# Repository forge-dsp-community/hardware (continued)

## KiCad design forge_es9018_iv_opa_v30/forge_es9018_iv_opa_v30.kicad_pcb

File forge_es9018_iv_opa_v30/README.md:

# Forge ES9018 I/V-Ausgangsplatine V3.0 (96ELN) – KiCad-Rekonstruktion

| Seite F | Seite B |
|---|---|
|  |  |

3D-Renderings aus KiCad (`kicad-cli pcb render --rotate '-35,0,±30' --zoom 0.9 --background opaque`). C5…C8 sind wie auf den realen Platinen 0-Ω-Brücken auf den Elko-Plätzen.

## Herkunft

Quelle: `forge/pcbs/output/eln/V30` (bitbucket.org/forge-dsp/pcbs, Mark Duprau, Lizenz CC BY-NC-SA 4.0).
Diese Rekonstruktion steht unter derselben Lizenz.

Diese I/V-Ausgangsplatine wird in einen der 4 Steckplätze J1–J4 der AD/DA-Trägerplatine gesteckt
(siehe `../forge_es9018_pcm4202_ad_v40`). Dort sitzt der ES9018 bzw. ES90x8.
Die Platine wandelt zwei differentielle DAC-Stromausgänge in zwei symmetrische Spannungsausgänge um.

## Schaltung (je Kanal, Kanal 2 / Kanal 1)

| Stufe | Bauteile | Wert |
|---|---|---|
| I/V-Wandler (+ Eingang an I.x-VREF) | R1/R2 bzw. R5/R6 (Rückkopplung) | 2720R 0.1% 10ppm |
| | R102…R105 + C116…C119 (Serienglied parallel zur Rückkopplung) | 100R 0.1% + 100pF C0G |
| Elkoplatz, mit 0R überbrückt (nur V30) | C5…C8 zwischen I/V-Ausgang und 470R | Auf realen Platinen mit 0-Ω-SMD (1206) auf den THT-Pads bestückt statt mit Elko |
| Filter | R106…R109 / C1…C4 | 470R 0.1% / 100nF C0G |
| Differenzverstärker | R114…R117 (Eingang), R110…R113 (Rückkopplung bzw. nach AGND) | 20R 1% / 360R 0.1% |
| | C122…C125 + R3, R4, R7, R8 | 3.9nF C0G + 100R 0.1% |
| VREF-Abblockung | C9, C10 | Wert im Original nicht angegeben |
| Versorgung | C110…C115 | 100nF 16V |

Steckzunge X1 (13 Kontakte, links → rechts): O.2+, O.2−, O.1+, O.1−, −12V, GND, +12V, I.1−, I.1−VREF, I.1+, I.2−, I.2−VREF, I.2+.
O.x− und GND liegen auf AGND.

## Vorgehen

* Quelle sind nur die Eagle-Renderings im Repo (300 dpi): Kupferlagen, Vias, Durchsteckpads (`PADS`), Bestückungsdruck, das Gesamtbild und das Schaltplanbild. Gerber-Bilder gibt es für diese Platine nicht.
* SMD-Pads und Bauteilmitten stammen aus dem Gesamtbild, SOIC-Gehäuse aus den Pinreihen.
  Die Opamp-Ausrichtung ergibt sich aus den ±12-V-Kontakten der Steckzunge.
* Netze ergeben sich aus den Kupfer-Inseln je Lage, verbunden über Vias.
* **Referenzen und Werte** wurden über die Schaltungstopologie den Originalbezeichnungen zugeordnet.
  Beispiel: Ein Widerstand zwischen dem − Eingang und dem Ausgang einer I/V-Sektion ist R1/R2/R5/R6.
  Alle 48 passiven Bauteile des Original-Schaltplans wurden gefunden und zugeordnet.
* Kupfer liegt als **Leiterbahnen** vor (463 Leiterbahn-Segmente, 66 Flächen-Zonen). Breite Flächen (im Original Eagle-Polygone, auch Via-Felder) sind **Zonen mit Netz**, die KiCad selbst füllt (Clearance 0,08 mm, Thermals an THT-Pads). Schaltplan und Platine sind verknüpft.
  Erzeugt mit `rekonstruktion/tracks.py` aus `polys.json`:
  Jede Kupferinsel wird mit 25 px/mm gerastert. Flächen werden über den Distanz-Transform erkannt (morphologisches Öffnen), der Rest wird skelettiert (Zhang-Suen), in Pfade zwischen End- und Knotenpunkten zerlegt, mit Douglas-Peucker vereinfacht, kurze Sporne fallen weg.
  Spurbreite = 2 × Distanz-Transform (Median), abgerundet auf Eagle-Breiten (0,1524 … 1,016 mm) und zusätzlich so begrenzt, dass Clearance zu fremdem Kupfer und Randabstand passen. Über das eigene Kupfer hinaus darf eine Spur höchstens bis zur Hälfte der Lücke zum Nachbarn ragen.
  Endpunkte an Pads/Vias desselben Netzes rasten auf die Pad-/Via-Mitte ein, an Flächen werden sie 0,3 mm hinein verlängert.
  Fläche wird, was einschließlich Pads und Vias ≥ 1,2 mm breit ist, dazu angrenzendes Kupfer ab 0,9 mm Breite. Danach rastert das Skript die erzeugten Spuren und vergleicht sie mit dem Originalkupfer (Formprüfung): Bleibt ein dicker Bereich (≥ 0,3 mm dick, ≥ 0,15 mm²) unbedeckt, wird er mit 0,5 mm Umgebung zur Fläche und die Insel neu berechnet. So werden Via-Felder Flächen statt Haufen kurzer breiter Spuren.
  Die Bild-Pads sind oft größer als die Footprint-Pads, manche Vias liegen direkt am Pad. Was nach dem Skelett innerhalb einer Insel noch getrennt ist, verbindet das Skript deshalb über einen kürzesten Weg durch das Originalkupfer.
  Zum Schluss prüft das Skript mit dem KiCad-DRC und macht Spuren mit Clearance- oder Randfehlern schrittweise schmaler. Spuren, die schon 0,1 mm breit sind, schiebt es um das fehlende Stück vom Hindernis weg.
  Die frühere Zonen-Fassung liegt als `rekonstruktion/forge_es9018_iv_opa_v30_zonen.kicad_pcb` bei. Neu erzeugen mit `/usr/bin/python3 rekonstruktion/tracks.py .`; das Skript liest immer die Zonen-Fassung.

## Prüfung

* DRC (`kicad-cli pcb drc --refill-zones --schematic-parity`): keine offenen Verbindungen, keine Kurzschlüsse, keine Clearance-Fehler, Schaltplan-Abgleich ohne Abweichungen, also wie mit den Zonen.
  Warnungen: 12 × Druck über Kupfer bzw. am Rand (Original-Bestückungsdruck), 4 × „Leiterbahn mit offenem Ende“. Das sind Sackgassen im Originalkupfer (Masse-Randstreifen, AGND-Finger).
* ERC: 0 Verstöße

## Schaltplan

`rekonstruktion/sch_layout.py` ordnet den aus `sch.py` erzeugten Schaltplan neu an (A3):

* OpAmps sind IC-Kästen mit allen 8 bzw. 14 Pins in Gehäusefolge (links 1…4 bzw. 1…7 von oben, rechts gegenläufig). Die Symbole `OPA_DUAL`/`OPA_QUAD` in `forge_iv_opa.kicad_sym` wurden dafür ersetzt.
* Je OpAmp-Sektion liegt die Rückkopplung (R, RC-Glied) außen neben ihren drei Pins, auf der Seite des Ausgangs. Vom Ausgang laufen Koppel-C, Filterwiderstand und Filterknoten mit Querkondensator in einer Reihe nach außen. Die Eingangsbeschaltung liegt auf der anderen Seite.
* Die Abblockkondensatoren hängen per Draht am V+/V−-Pin des OpAmps, an dem sie auf der Platine sitzen.
* Globale Labels gibt es nur zwischen den Gruppen (OpAmp-Blöcke und Steckzunge X1). Versorgung erscheint als Power-Symbole.
* Verdrahtete Netze tragen ihren Namen als lokales Label (`/NAME`). Die Netznamen der Platine sind daran angeglichen (`sch_layout.py <projekt> --pcb`, ändert `.kicad_pcb` und die Zonen-Sicherung). Der DRC mit Schaltplan-Abgleich ist ohne Abweichung.
* Die Netzliste ist geprüft identisch mit der vorherigen Label-Fassung (`rekonstruktion/<name>_labels.kicad_sch`). Die ERC ist ohne Fehler.

## Hinweise

* 2 Lagen. **U2 = LME49740** (Quad, SOIC-14, alle 4 I/V-Stufen, V+ an Pin 4, V− an Pin 11).
  **U1 = LME49720** (Dual, SOIC-8, Differenzverstärker beider Kanäle, V+ an Pin 8, V− an Pin 4).
  Die Typen stammen vom Nutzer. Die Pinbelegung ist gegen beide Datenblätter geprüft (LME49720 von TI, LME49740 von National, Connection Diagram):
  V+/V− und alle + Eingänge (VREF) bzw. − Eingänge (I.x±) liegen auf den Pins, die die Datenblätter angeben.
  Das Datenblatt-Feld ist in Symbol und Footprint eingetragen.
* C5…C8 sind im Bestückungsdruck Elko-Plätze (Plus zum 470R, quadratisches Pad Minus). Auf realen Platinen sitzt dort aber ein 0-Ω-SMD-Widerstand, die I/V-Stufen sind also DC-gekoppelt; den Gleichanteil hebt der Differenzverstärker auf. Schaltplan (Symbol R, Wert „0R (Brücke)“), Footprint `R_0R_auf_Elkoplatz_TH_P2.55` (Elko-Pads, 3D-Modell 1206) und die Generatoren (`outnaming.py`, `pcb.py`, `sch.py`, `models3d.py`) bilden das ab. Die Netze IVx±/IVx±_AC bleiben getrennt benannt.
* Die Symbole sind generische Dual-/Quad-OpAmp-Symbole (IC-Kasten mit allen Pins in Gehäusefolge) mit den Pinfunktionen nach Datenblatt; der Wert trägt den Typ.
* Einige SMD-Pads liegen teilweise unter dem Bestückungsdruck. Ihre Größe ist aus dem Bild geschätzt (±0,05 mm); die Pad-Mitten passen zum Kupfer.
* Skripte und Modell liegen in `rekonstruktion/`. Neu erzeugen mit `build_out.sh V30` (ergibt die Zonen-Fassung), danach `rekonstruktion/forge_es9018_iv_opa_v30_zonen.kicad_pcb` löschen und `/usr/bin/python3 rekonstruktion/tracks.py .` ausführen; die Pfade in `build_out.sh` zeigen auf das temporäre Arbeitsverzeichnis der Sitzung.

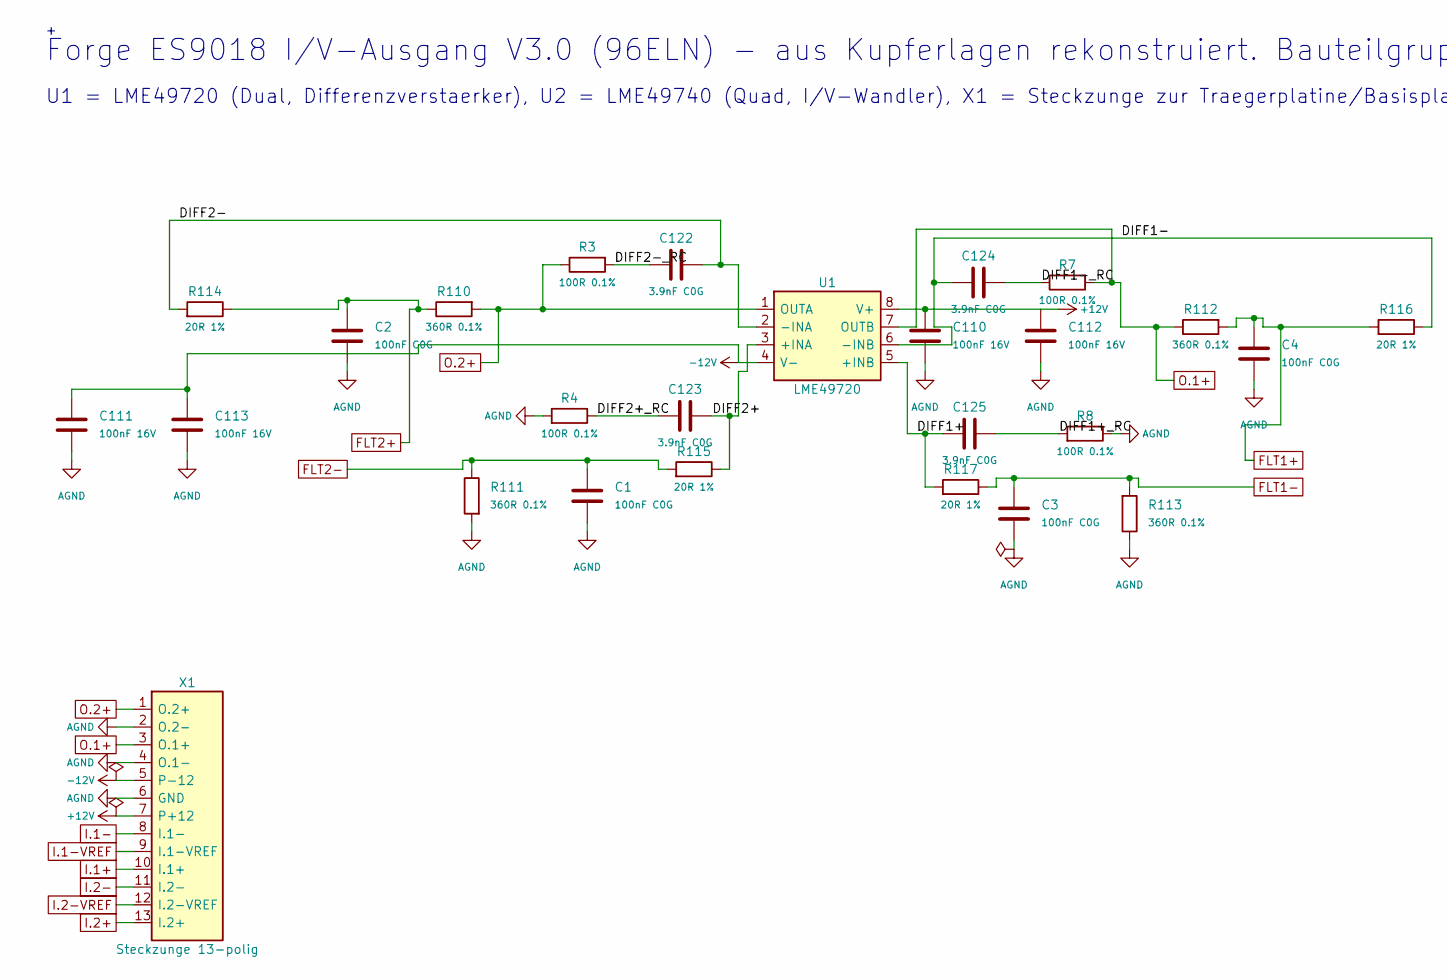
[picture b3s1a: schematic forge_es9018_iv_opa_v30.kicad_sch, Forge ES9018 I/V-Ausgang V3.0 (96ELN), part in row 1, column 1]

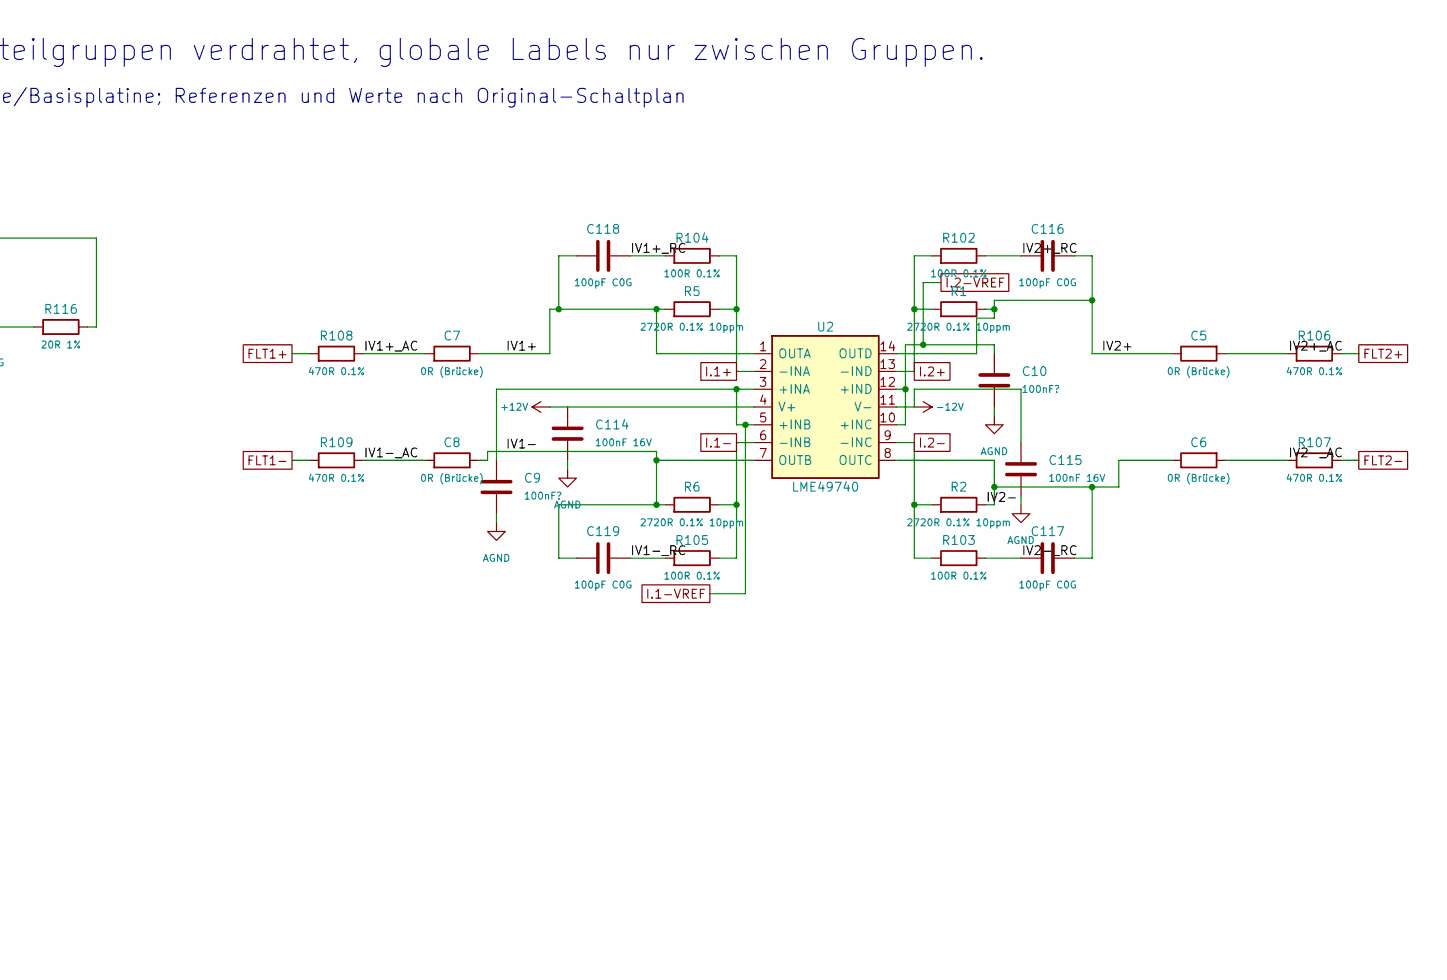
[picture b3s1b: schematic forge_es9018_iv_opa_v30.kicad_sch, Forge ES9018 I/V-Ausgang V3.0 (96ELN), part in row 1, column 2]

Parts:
C1, C3, C4: 100nF C0G; RC_1206_Eagle_P1.30
C2: 100nF C0G; RC_1206_Eagle_P1.35
C5, C6, C7, C8: 0R (Brücke); R_0R_auf_Elkoplatz_TH_P2.55
C9, C10: 100nF?; RC_1206_Eagle_P1.35
C110, C111, C114, C115: 100nF 16V; RC_1206_Eagle_P1.35
C112, C113: 100nF 16V; RC_1210_Eagle_P2.65
C116, C118: 100pF C0G; RC_1206_Eagle_P1.25
C117, C119: 100pF C0G; RC_1206_Eagle_P1.30
C122, C124, C125: 3.9nF C0G; RC_1206_Eagle_P1.35
C123: 3.9nF C0G; RC_1206_Eagle_P1.30
R1, R2, R5, R6: 2720R 0.1% 10ppm; RC_0603_Eagle_P1.25
R3: 100R 0.1%; RC_0603_Eagle_P1.20
R4, R7, R8, R102, R103, R104, R105: 100R 0.1%; RC_0603_Eagle_P1.25
R106, R107, R108: 470R 0.1%; RC_0603_Eagle_P1.15
R109: 470R 0.1%; RC_0603_Eagle_P1.20
R110, R111, R113: 360R 0.1%; RC_0603_Eagle_P1.25
R112: 360R 0.1%; RC_0603_Eagle_P1.15
R114, R115, R116, R117: 20R 1%; RC_0603_Eagle_P1.25
U1: LME49720; SOIC-8_Eagle
U2: LME49740; SOIC-14_Eagle
X1: Steckzunge 13-polig; Steckzunge_13pol_Forge_IV

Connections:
+12V: C110.2, C112.1, C114.2, U1.8 (V+), U2.4 (V+), X1.7 (P+12)
-12V: C111.1, C113.1, C115.1, U1.4 (V-), U2.11 (V-), X1.5 (P-12)
/DIFF1+: C125.1, R117.1, U1.5 (+INB)
/DIFF1+_RC: C125.2, R8.1
/DIFF1-: C124.2, R116.2, U1.6 (-INB)
/DIFF1-_RC: C124.1, R7.2
/DIFF2+: C123.1, R115.2, U1.3 (+INA)
/DIFF2+_RC: C123.2, R4.2
/DIFF2-: C122.1, R114.1, U1.2 (-INA)
/DIFF2-_RC: C122.2, R3.1
/IV1+: C7.2, C118.1, R5.1, U2.1 (OUTA)
/IV1+_AC: C7.1, R108.2
/IV1+_RC: C118.2, R104.1
/IV1-: C8.2, C119.1, R6.1, U2.7 (OUTB)
/IV1-_AC: C8.1, R109.2
/IV1-_RC: C119.2, R105.1
/IV2+: C5.2, C116.2, R1.2, U2.14 (OUTD)
/IV2+_AC: C5.1, R106.1
/IV2+_RC: C116.1, R102.2
/IV2-: C6.2, C117.1, R2.2, U2.8 (OUTC)
/IV2-_AC: C6.1, R107.1
/IV2-_RC: C117.2, R103.2
AGND: C1.2, C2.1, C3.1, C4.2, C9.1, C10.2, C110.1, C111.2, C112.2, C113.2, C114.1, C115.2, R4.1, R8.2, R111.1, R113.2, X1.2 (O.2-), X1.4 (O.1-), X1.6 (GND)
FLT1+: C4.1, R108.1, R112.1, R116.1
FLT1-: C3.2, R109.1, R113.1, R117.2
FLT2+: C2.2, R106.2, R110.2, R114.2
FLT2-: C1.1, R107.2, R111.2, R115.1
I.1+: R5.2, R104.2, U2.2 (-INA), X1.10 (I.1+)
I.1-: R6.2, R105.2, U2.6 (-INB), X1.8 (I.1-)
I.1-VREF: C9.2, U2.3 (+INA), U2.5 (+INB), X1.9 (I.1-VREF)
I.2+: R1.1, R102.1, U2.13 (-IND), X1.13 (I.2+)
I.2-: R2.1, R103.1, U2.9 (-INC), X1.11 (I.2-)
I.2-VREF: C10.1, U2.10 (+INC), U2.12 (+IND), X1.12 (I.2-VREF)
O.1+: R7.1, R112.2, U1.7 (OUTB), X1.3 (O.1+)
O.2+: R3.2, R110.1, U1.1 (OUTA), X1.1 (O.2+)

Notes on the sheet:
Forge ES9018 I/V-Ausgang V3.0 (96ELN) - aus Kupferlagen rekonstruiert. Bauteilgruppen verdrahtet, globale Labels nur zwischen Gruppen.
U1 = LME49720 (Dual, Differenzverstaerker), U2 = LME49740 (Quad, I/V-Wandler), X1 = Steckzunge zur Traegerplatine/Basisplatine; Referenzen und Werte nach Original-Schaltplan

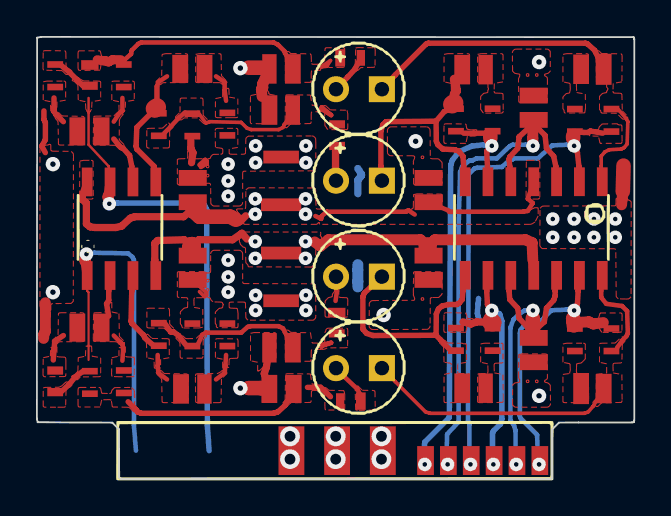
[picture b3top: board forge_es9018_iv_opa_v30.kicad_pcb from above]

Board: 4 copper layers, 33.2 x 24.6 mm, 51 parts (0 on the bottom side), 35 nets.

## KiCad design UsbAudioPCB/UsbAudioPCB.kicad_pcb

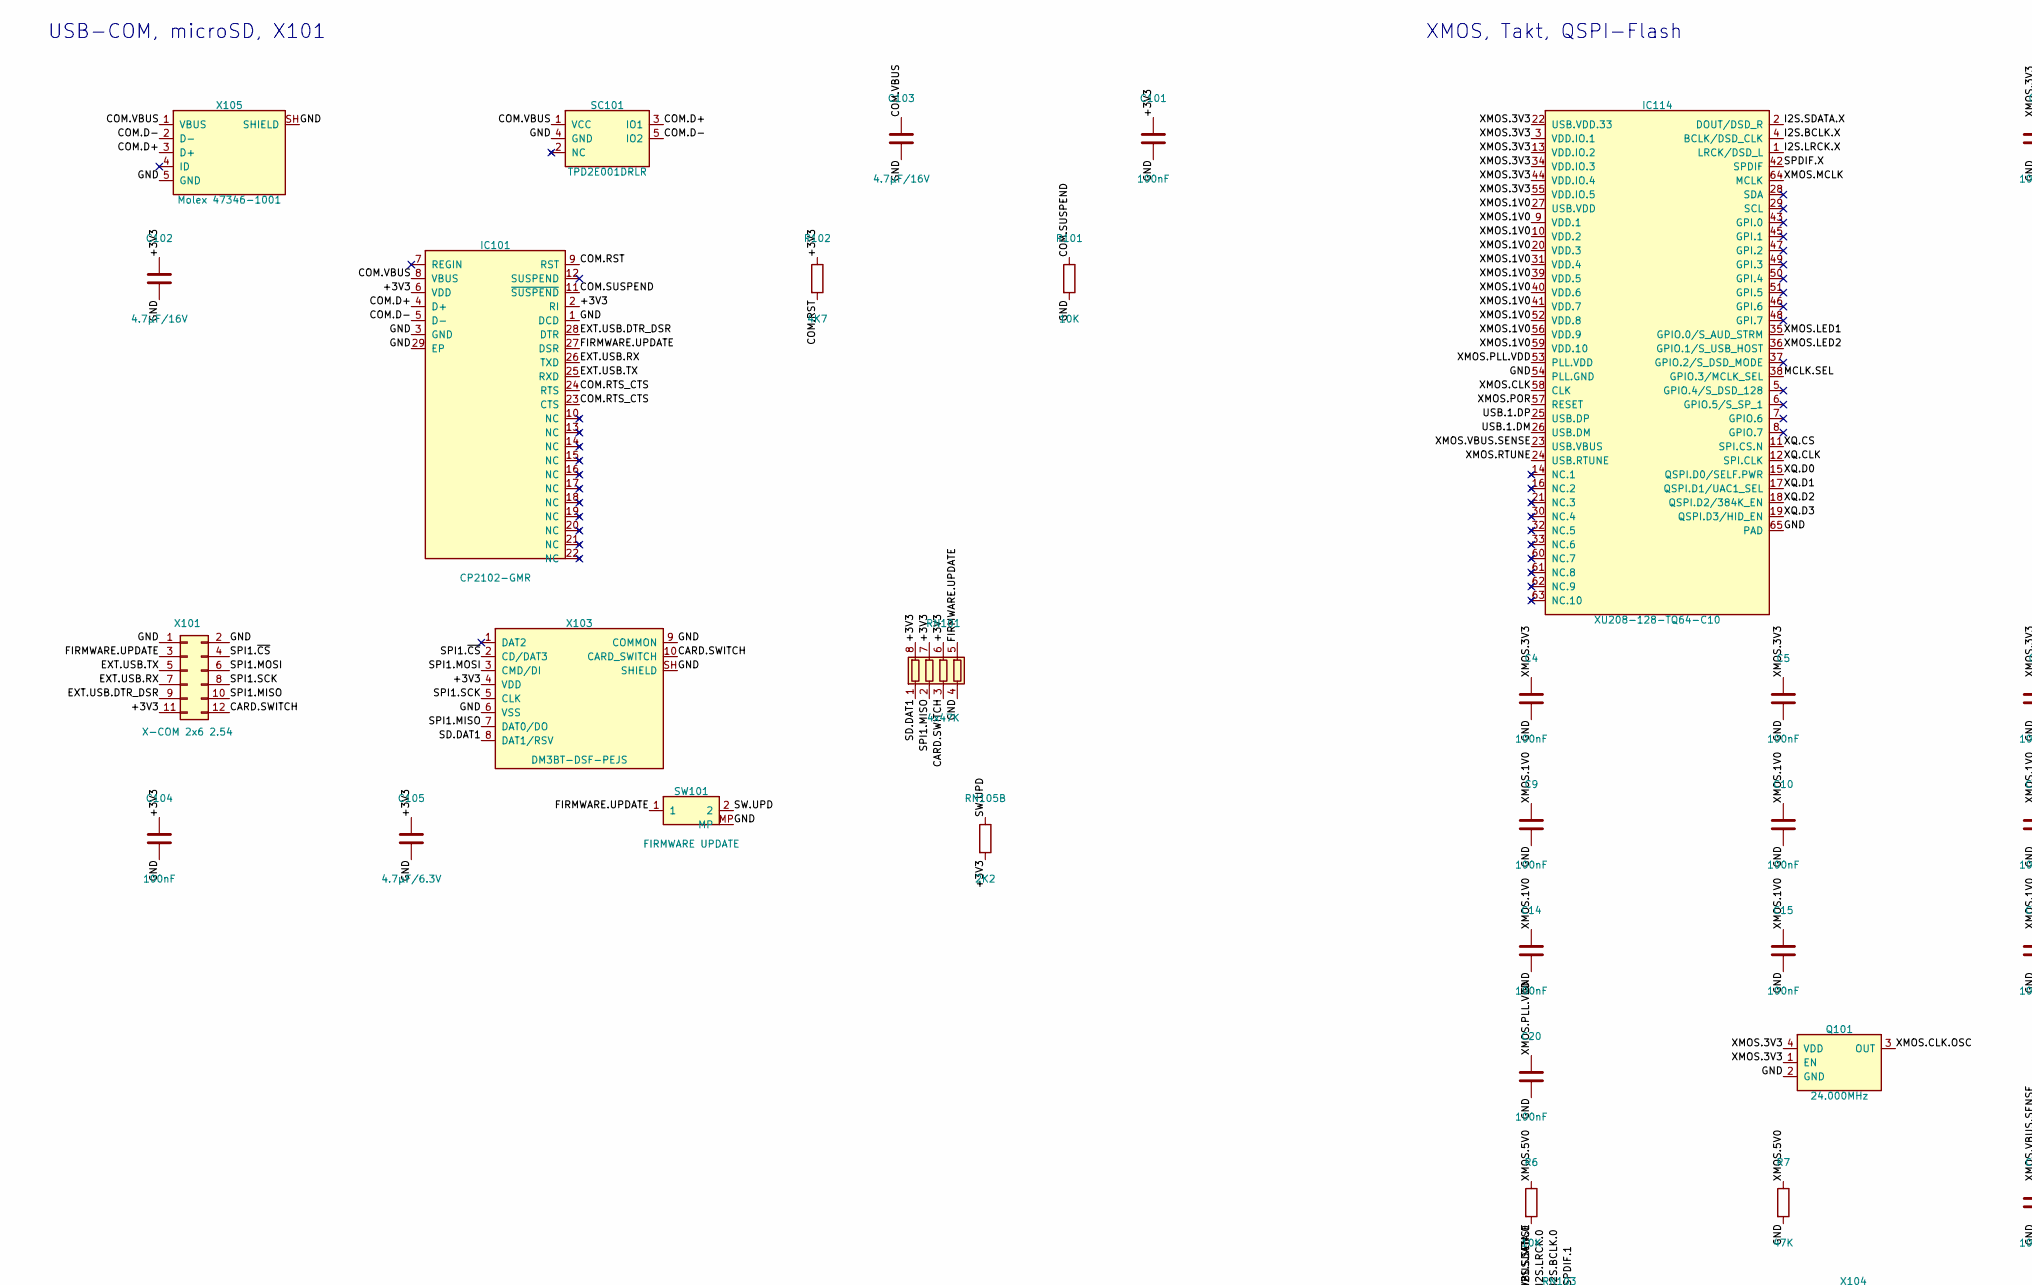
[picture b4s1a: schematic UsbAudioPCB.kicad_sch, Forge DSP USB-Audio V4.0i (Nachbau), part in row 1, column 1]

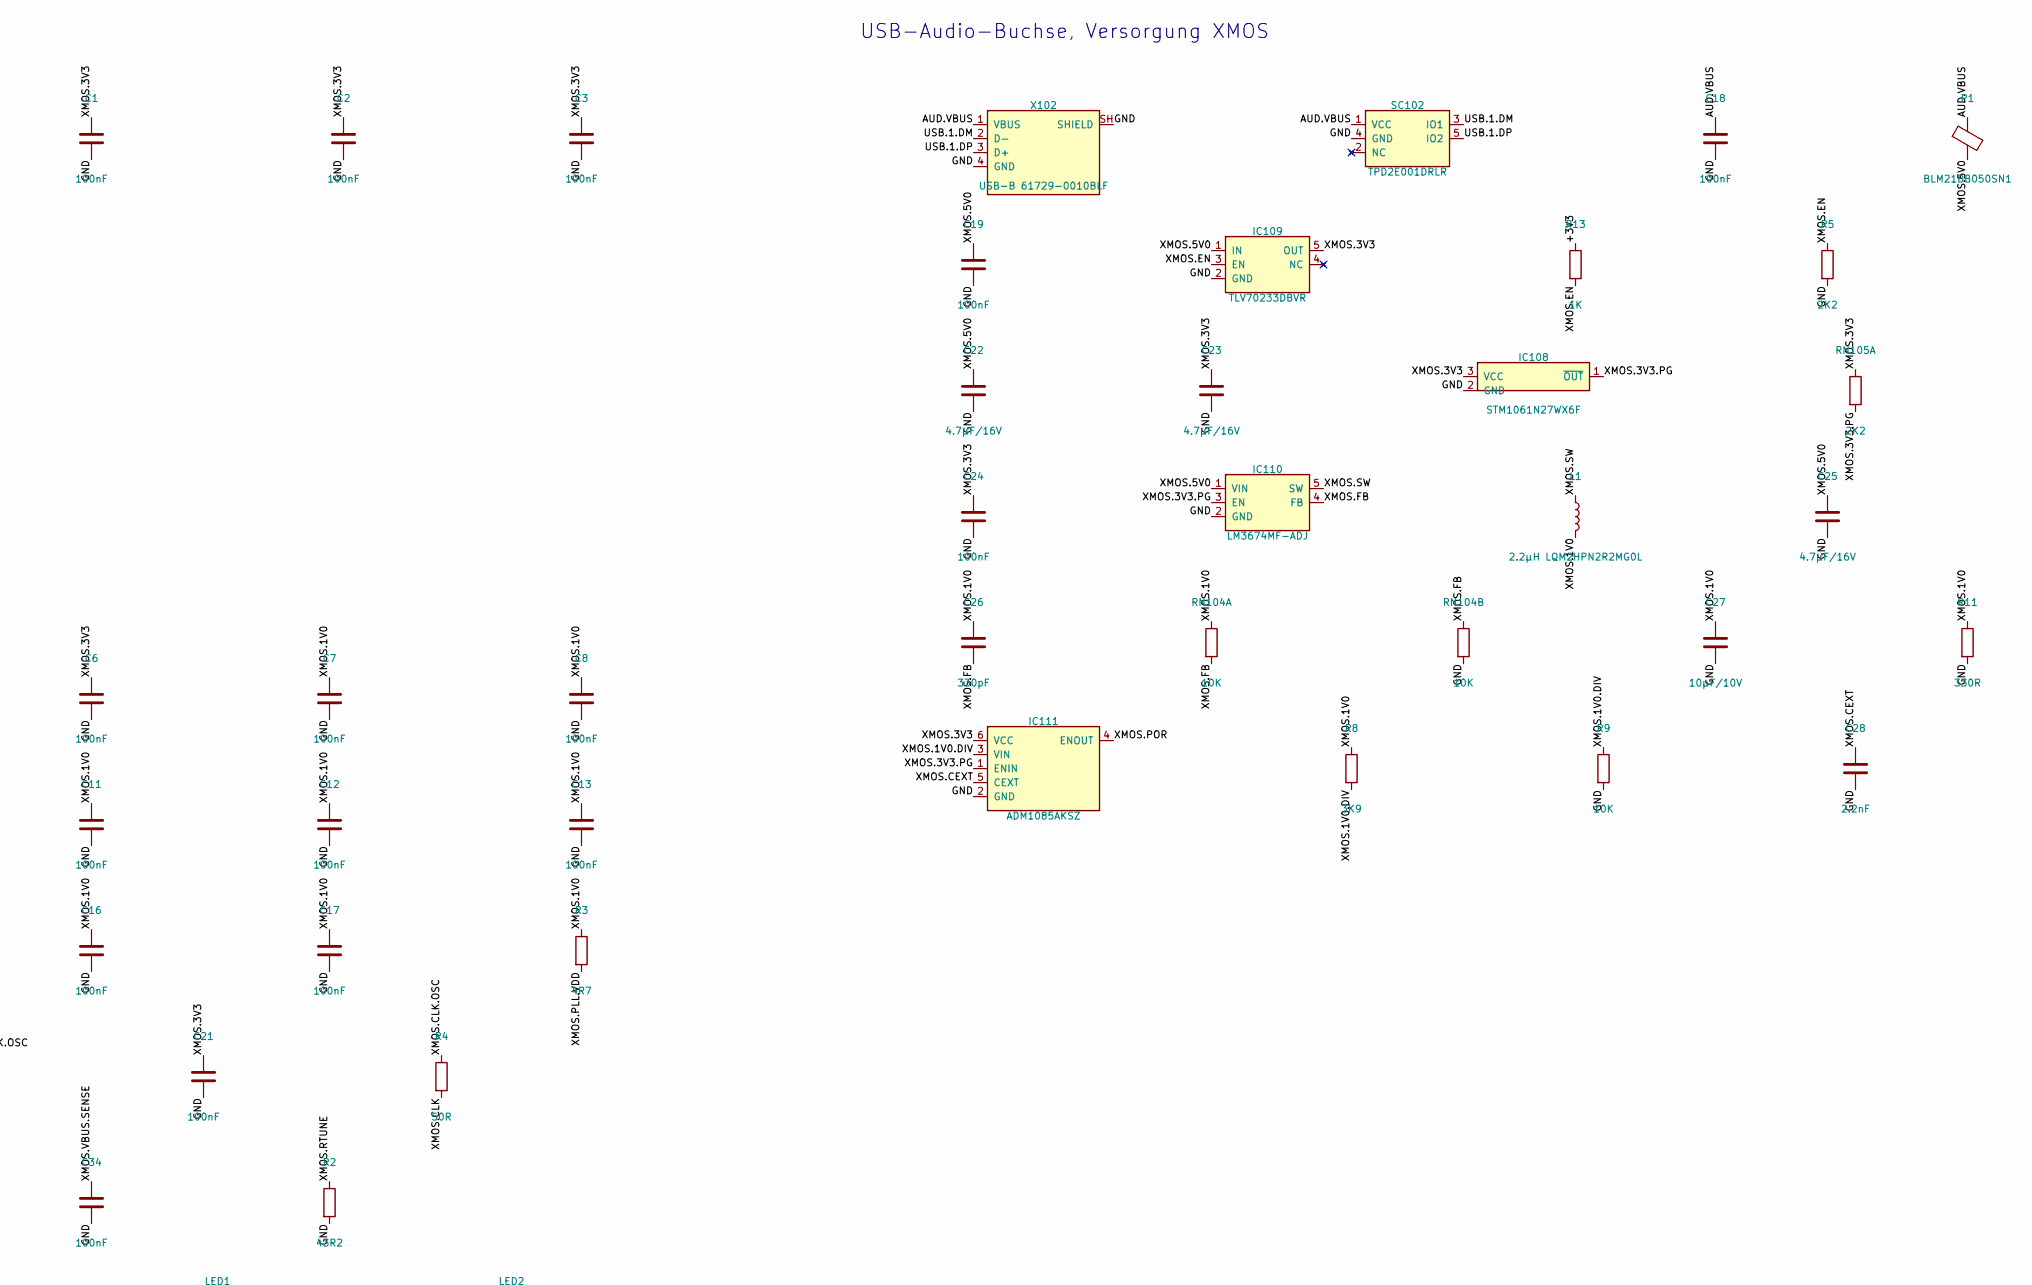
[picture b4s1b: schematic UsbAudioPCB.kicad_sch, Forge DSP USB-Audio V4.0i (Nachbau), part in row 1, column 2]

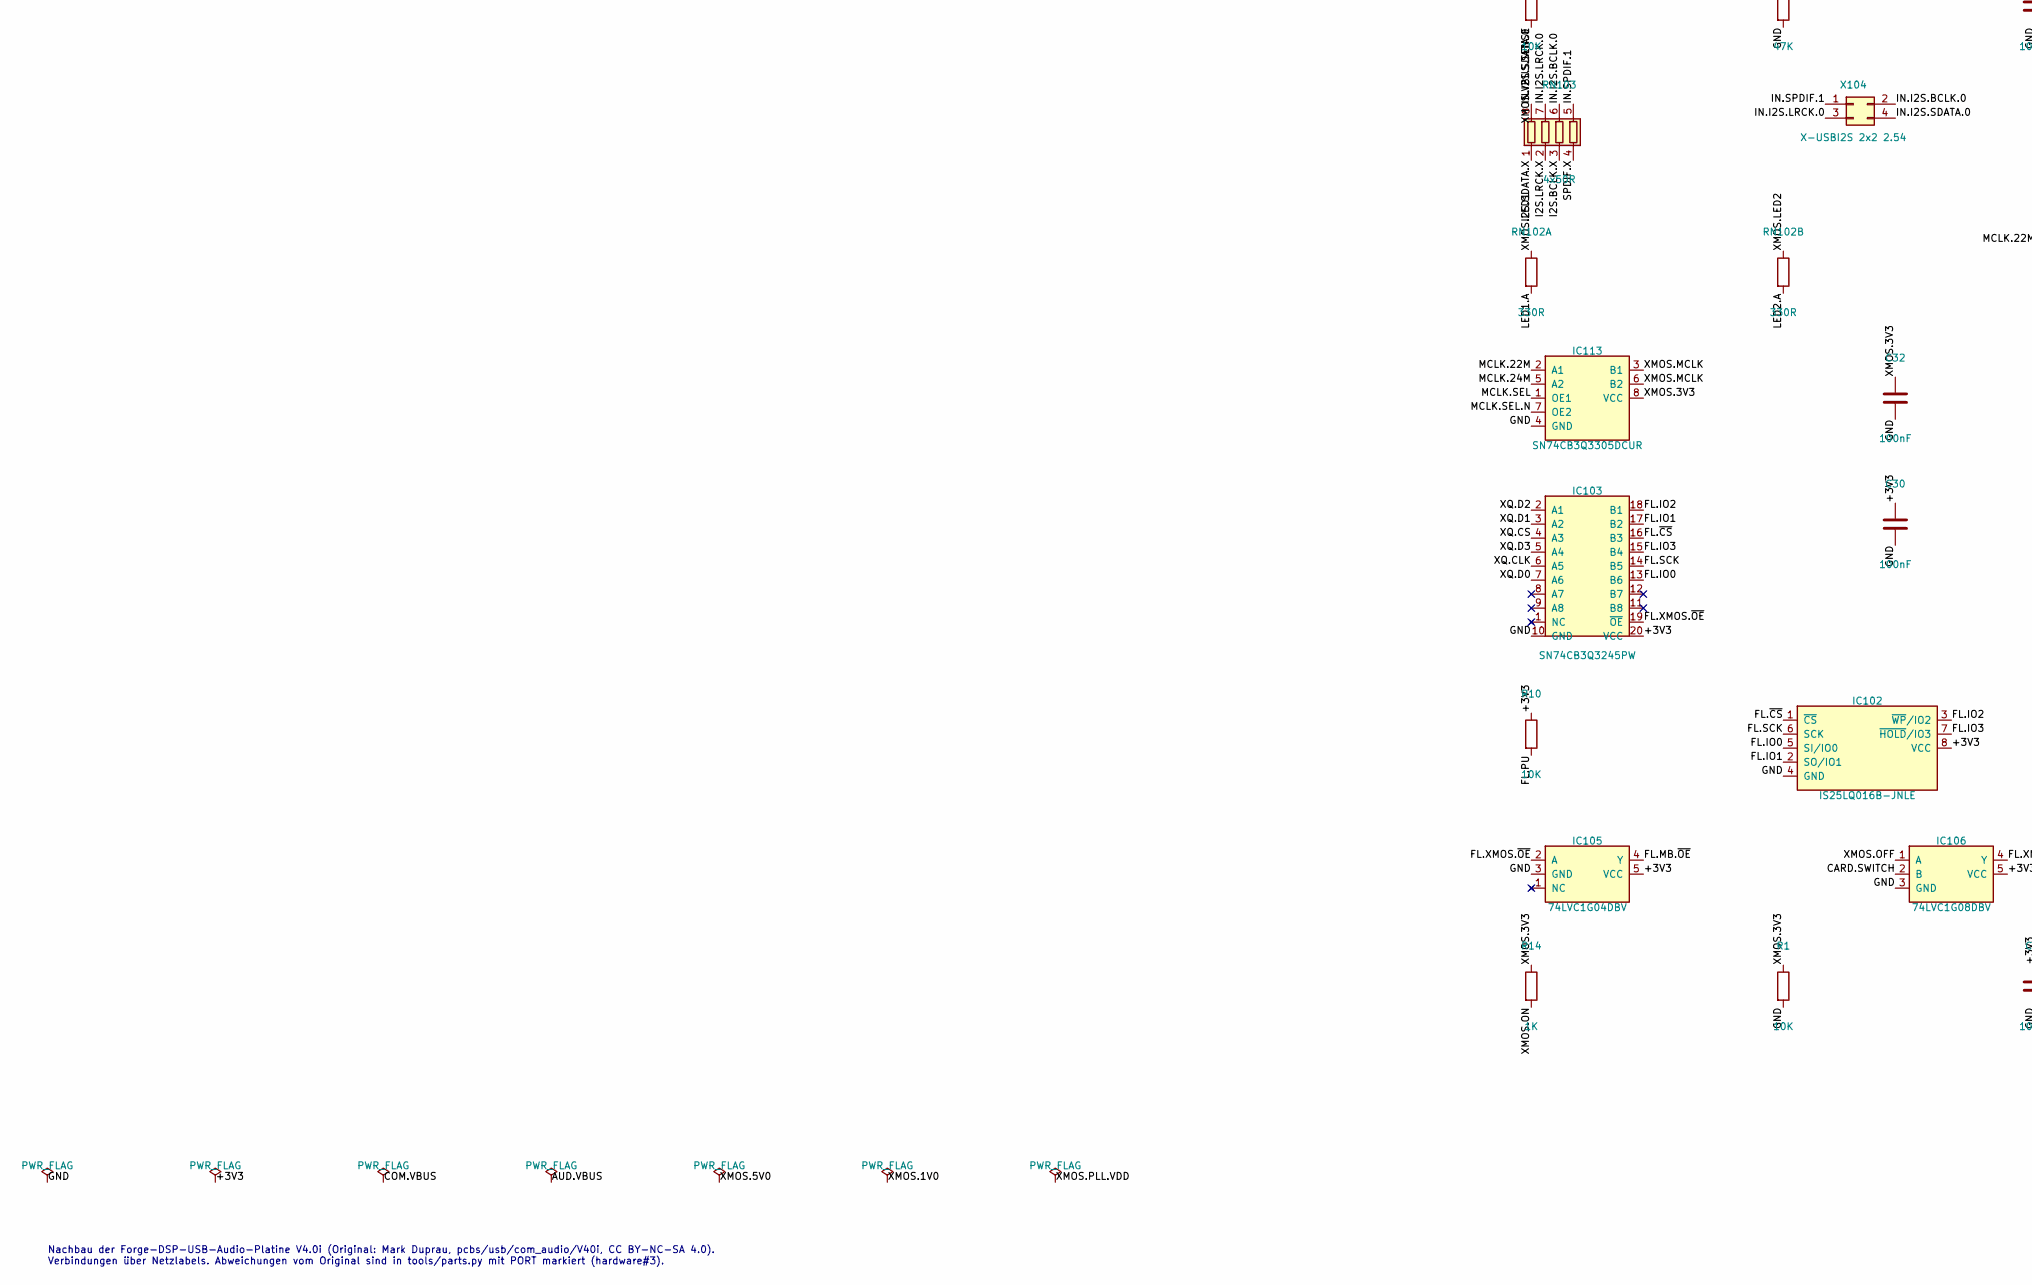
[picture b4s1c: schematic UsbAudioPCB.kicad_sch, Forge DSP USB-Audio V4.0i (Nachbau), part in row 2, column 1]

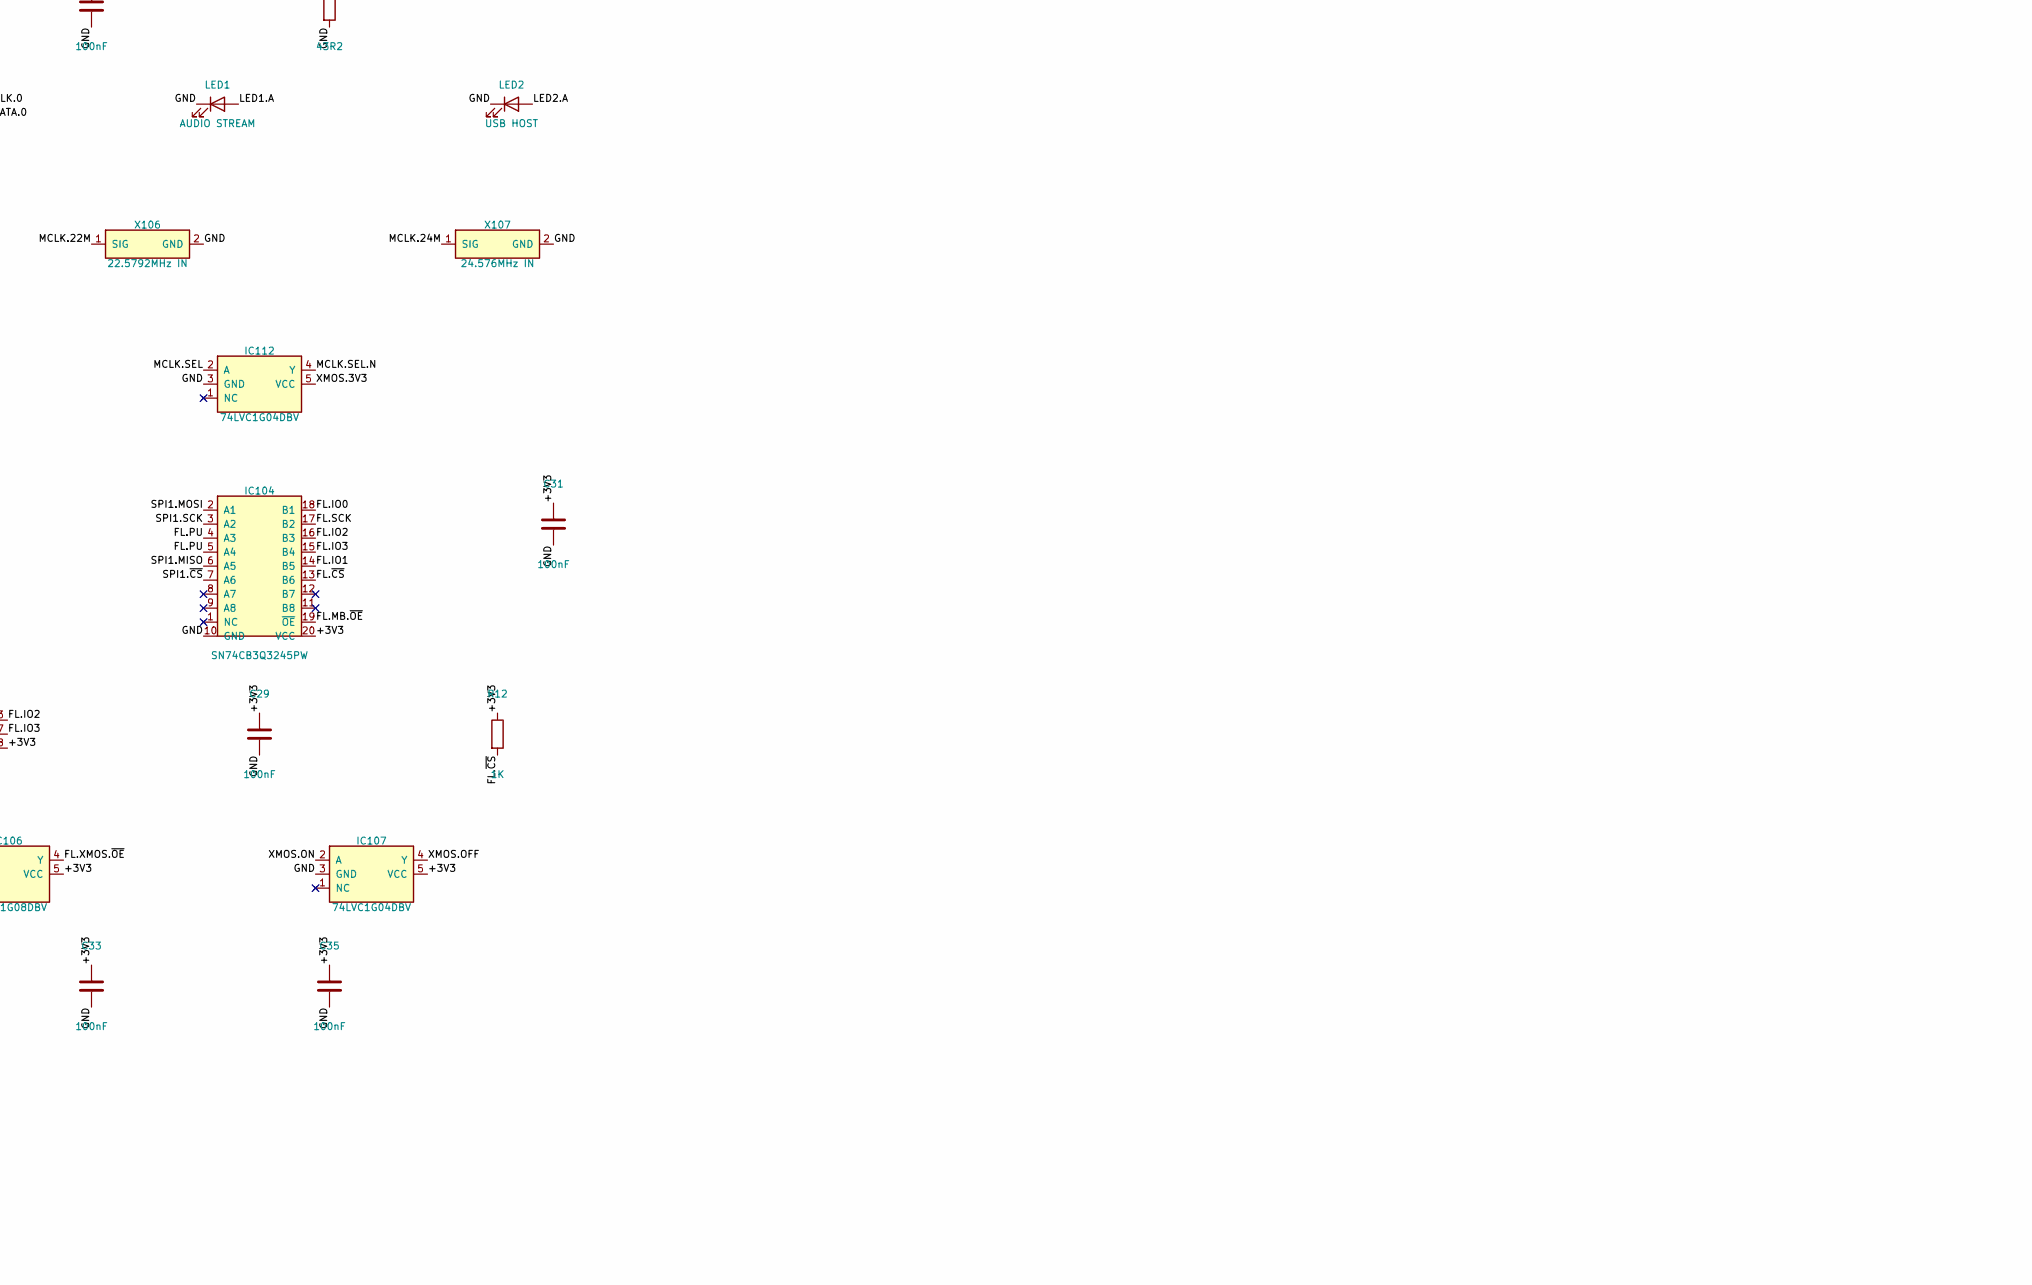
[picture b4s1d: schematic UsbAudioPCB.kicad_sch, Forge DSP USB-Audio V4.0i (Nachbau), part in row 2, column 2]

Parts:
C1, C2, C3, C4, C5, C6, C7, C8, C9, C10, C11, C12, C13, C14, C15, C16, C17, C18, C19, C20, C21, C24, C29, C30, C31, C32, C33, C34, C35, C101, C104: 100nF; C_0603_1608Metric
C22, C23, C25, C102, C103: 4.7µF/16V; C_0805_2012Metric
C26: 330pF; C_0603_1608Metric
C27: 10µF/10V; C_0805_2012Metric
C28: 2.2nF; C_0603_1608Metric
C105: 4.7µF/6.3V; C_0805_2012Metric
IC101: CP2102-GMR; QFN-28-1EP_5x5mm_P0.5mm_EP3.35x3.35mm
IC102: IS25LQ016B-JNLE; SOIC-8_3.9x4.9mm_P1.27mm
IC103, IC104: SN74CB3Q3245PW; TSSOP-20_4.4x6.5mm_P0.65mm
IC105, IC107, IC112: 74LVC1G04DBV; SOT-23-5
IC106: 74LVC1G08DBV; SOT-23-5
IC108: STM1061N27WX6F; SOT-23
IC109: TLV70233DBVR; SOT-23-5
IC110: LM3674MF-ADJ; SOT-23-5
IC111: ADM1085AKSZ; SOT-363_SC-70-6
IC113: SN74CB3Q3305DCUR; VSSOP-8_2.3x2mm_P0.5mm
IC114: XU208-128-TQ64-C10; TQFP-64-1EP_10x10mm_P0.5mm_EP5.305x5.305mm_ThermalVias
L1: 2.2µH LQM2HPN2R2MG0L; L_1008_2520Metric
LED1: AUDIO STREAM; LED_0603_1608Metric
LED2: USB HOST; LED_0603_1608Metric
P1: BLM21BB050SN1; L_0805_2012Metric
Q101: 24.000MHz; Oscillator_SMD_Abracon_ASE-4Pin_3.2x2.5mm
R1, R6, R9, R10, R101: 10K; R_0603_1608Metric
R2: 43R2; R_0603_1608Metric
R3: 4R7; R_0603_1608Metric
R4: 50R; R_0603_1608Metric
R5: 2K2; R_0603_1608Metric
R7: 47K; R_0603_1608Metric
R8: 3K9; R_0603_1608Metric
R11: 330R; R_0603_1608Metric
R12, R13, R14: 1K; R_0603_1608Metric
R102: 4K7; R_0603_1608Metric
RN101: 4x47K; R_Array_Convex_4x0603
RN102A, RN102B: 330R; R_0603_1608Metric
RN103: 4x50R; R_Array_Convex_4x0603
RN104A, RN104B: 10K; R_0603_1608Metric
RN105A, RN105B: 2K2; R_0603_1608Metric
SC101, SC102: TPD2E001DRLR; SOT-553
SW101: FIRMWARE UPDATE; SW_Push_1P1T-MP_NO_Horizontal_Alps_SKRTLAE010
X101: X-COM 2x6 2.54; PinHeader_2x06_P2.54mm_Vertical
X102: USB-B 61729-0010BLF; USB_B_OST_USB-B1HSxx_Horizontal
X103: DM3BT-DSF-PEJS; microSD_HC_Hirose_DM3BT-DSF-PEJS
X104: X-USBI2S 2x2 2.54; PinHeader_2x02_P2.54mm_Vertical
X105: Molex 47346-1001; USB_Micro-B_Molex_47346-0001
X106: 22.5792MHz IN; U.FL_Hirose_U.FL-R-SMT-1_Vertical; LCSC C88373
X107: 24.576MHz IN; U.FL_Hirose_U.FL-R-SMT-1_Vertical; LCSC C88373

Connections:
+3V3: C29.1, C30.1, C31.1, C33.1, C35.1, C101.1, C102.1, C104.1, C105.1, IC101.2 (RI), IC101.6 (VDD), IC102.8 (VCC), IC103.20 (VCC), IC104.20 (VCC), IC105.5 (VCC), IC106.5 (VCC), IC107.5 (VCC), R10.1, R12.1, R13.1, R102.1, RN101.6 (R3.2), RN101.7 (R2.2), RN101.8 (R1.2), RN105B.2, X101.11, X103.4 (VDD)
AUD.VBUS: C18.1, P1.1, SC102.1 (VCC), X102.1 (VBUS)
CARD.SWITCH: IC106.2 (B), RN101.3 (R3.1), X101.12, X103.10 (CARD_SWITCH)
COM.D+: IC101.4 (D+), SC101.3 (IO1), X105.3 (D+)
COM.D-: IC101.5 (D-), SC101.5 (IO2), X105.2 (D-)
COM.RST: IC101.9 (RST), R102.2
COM.RTS_CTS: IC101.23 (CTS), IC101.24 (RTS)
COM.SUSPEND: IC101.11 (~SUSPEND), R101.1
COM.VBUS: C103.1, IC101.8 (VBUS), SC101.1 (VCC), X105.1 (VBUS)
EXT.USB.DTR_DSR: IC101.28 (DTR), X101.9
EXT.USB.RX: IC101.26 (TXD), X101.7
EXT.USB.TX: IC101.25 (RXD), X101.5
FIRMWARE.UPDATE: IC101.27 (DSR), RN101.5 (R4.2), SW101.1, X101.3
FL.IO0: IC102.5 (SI/IO0), IC103.13 (B6), IC104.18 (B1)
FL.IO1: IC102.2 (SO/IO1), IC103.17 (B2), IC104.14 (B5)
FL.IO2: IC102.3 (~WP/IO2), IC103.18 (B1), IC104.16 (B3)
FL.IO3: IC102.7 (~HOLD/IO3), IC103.15 (B4), IC104.15 (B4)
FL.MB.~OE: IC104.19 (~OE), IC105.4 (Y)
FL.PU: IC104.4 (A3), IC104.5 (A4), R10.2
FL.SCK: IC102.6 (SCK), IC103.14 (B5), IC104.17 (B2)
FL.XMOS.~OE: IC103.19 (~OE), IC105.2 (A), IC106.4 (Y)
FL.~CS: IC102.1 (~CS), IC103.16 (B3), IC104.13 (B6), R12.2
GND: C1.2, C2.2, C3.2, C4.2, C5.2, C6.2, C7.2, C8.2, C9.2, C10.2, C11.2, C12.2, C13.2, C14.2, C15.2, C16.2, C17.2, C18.2, C19.2, C20.2, C21.2, C22.2, C23.2, C24.2, C25.2, C27.2, C28.2, C29.2, C30.2, C31.2, C32.2, C33.2, C34.2, C35.2, C101.2, C102.2, C103.2, C104.2, C105.2, IC101.1 (DCD), IC101.3 (GND), IC101.29 (EP), IC102.4 (GND), IC103.10 (GND), IC104.10 (GND), IC105.3 (GND), IC106.3 (GND), IC107.3 (GND), IC108.2 (GND), IC109.2 (GND), IC110.2 (GND), IC111.2 (GND), IC112.3 (GND), IC113.4 (GND), IC114.54 (PLL.GND), IC114.65 (PAD), LED1.1 (K), LED2.1 (K), Q101.2 (GND), R1.2, R2.2, R5.2, R7.2, R9.2, R11.2, R101.2, RN101.4 (R4.1), RN104B.2, SC101.4 (GND), SC102.4 (GND), SW101.MP, X101.1, X101.2, X102.4 (GND), X102.SH (SHIELD), X103.6 (VSS), X103.9 (COMMON), X103.SH (SHIELD), X105.5 (GND), X105.SH (SHIELD), X106.2 (GND), X107.2 (GND)
I2S.BCLK.X: IC114.4 (BCLK/DSD_CLK), RN103.3 (R3.1)
I2S.LRCK.X: IC114.1 (LRCK/DSD_L), RN103.2 (R2.1)
I2S.SDATA.X: IC114.2 (DOUT/DSD_R), RN103.1 (R1.1)
IN.I2S.BCLK.0: RN103.6 (R3.2), X104.2
IN.I2S.LRCK.0: RN103.7 (R2.2), X104.3
IN.I2S.SDATA.0: RN103.8 (R1.2), X104.4
IN.SPDIF.1: RN103.5 (R4.2), X104.1
LED1.A: LED1.2 (A), RN102A.2
LED2.A: LED2.2 (A), RN102B.2
MCLK.22M: IC113.2 (A1), X106.1 (SIG)
MCLK.24M: IC113.5 (A2), X107.1 (SIG)
MCLK.SEL: IC112.2 (A), IC113.1 (OE1), IC114.38 (GPIO.3/MCLK_SEL)
MCLK.SEL.N: IC112.4 (Y), IC113.7 (OE2)
SD.DAT1: RN101.1 (R1.1), X103.8 (DAT1/RSV)
SPDIF.X: IC114.42 (SPDIF), RN103.4 (R4.1)
SPI1.MISO: IC104.6 (A5), RN101.2 (R2.1), X101.10, X103.7 (DAT0/DO)
SPI1.MOSI: IC104.2 (A1), X101.6, X103.3 (CMD/DI)
SPI1.SCK: IC104.3 (A2), X101.8, X103.5 (CLK)
SPI1.~CS: IC104.7 (A6), X101.4, X103.2 (CD/DAT3)
SW.UPD: RN105B.1, SW101.2
USB.1.DM: IC114.26 (USB.DM), SC102.3 (IO1), X102.2 (D-)
USB.1.DP: IC114.25 (USB.DP), SC102.5 (IO2), X102.3 (D+)
XMOS.1V0: C7.1, C8.1, C9.1, C10.1, C11.1, C12.1, C13.1, C14.1, C15.1, C16.1, C17.1, C26.1, C27.1, IC114.9 (VDD.1), IC114.10 (VDD.2), IC114.20 (VDD.3), IC114.27 (USB.VDD), IC114.31 (VDD.4), IC114.39 (VDD.5), IC114.40 (VDD.6), IC114.41 (VDD.7), IC114.52 (VDD.8), IC114.56 (VDD.9), IC114.59 (VDD.10), L1.2, R3.1, R8.1, R11.1, RN104A.1
XMOS.1V0.DIV: IC111.3 (VIN), R8.2, R9.1
XMOS.3V3: C1.1, C2.1, C3.1, C4.1, C5.1, C6.1, C21.1, C23.1, C24.1, C32.1, IC108.3 (VCC), IC109.5 (OUT), IC111.6 (VCC), IC112.5 (VCC), IC113.8 (VCC), IC114.3 (VDD.IO.1), IC114.13 (VDD.IO.2), IC114.22 (USB.VDD.33), IC114.34 (VDD.IO.3), IC114.44 (VDD.IO.4), IC114.55 (VDD.IO.5), Q101.1 (EN), Q101.4 (VDD), R1.1, R14.1, RN105A.1
XMOS.3V3.PG: IC108.1 (~OUT), IC110.3 (EN), IC111.1 (ENIN), RN105A.2
XMOS.5V0: C19.1, C22.1, C25.1, IC109.1 (IN), IC110.1 (VIN), P1.2, R6.1, R7.1
XMOS.CEXT: C28.1, IC111.5 (CEXT)
XMOS.CLK: IC114.58 (CLK), R4.2
XMOS.CLK.OSC: Q101.3 (OUT), R4.1
XMOS.EN: IC109.3 (EN), R5.1, R13.2
XMOS.FB: C26.2, IC110.4 (FB), RN104A.2, RN104B.1
XMOS.LED1: IC114.35 (GPIO.0/S_AUD_STRM), RN102A.1
XMOS.LED2: IC114.36 (GPIO.1/S_USB_HOST), RN102B.1
XMOS.MCLK: IC113.3 (B1), IC113.6 (B2), IC114.64 (MCLK)
XMOS.OFF: IC106.1 (A), IC107.4 (Y)
XMOS.ON: IC107.2 (A), R14.2
XMOS.PLL.VDD: C20.1, IC114.53 (PLL.VDD), R3.2
XMOS.POR: IC111.4 (ENOUT), IC114.57 (RESET)
XMOS.RTUNE: IC114.24 (USB.RTUNE), R2.1
XMOS.SW: IC110.5 (SW), L1.1
XMOS.VBUS.SENSE: C34.1, IC114.23 (USB.VBUS), R6.2
XQ.CLK: IC103.6 (A5), IC114.12 (SPI.CLK)
XQ.CS: IC103.4 (A3), IC114.11 (SPI.CS.N)
XQ.D0: IC103.7 (A6), IC114.15 (QSPI.D0/SELF.PWR)
XQ.D1: IC103.3 (A2), IC114.17 (QSPI.D1/UAC1_SEL)
XQ.D2: IC103.2 (A1), IC114.18 (QSPI.D2/384K_EN)
XQ.D3: IC103.5 (A4), IC114.19 (QSPI.D3/HID_EN)

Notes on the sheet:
USB-COM, microSD, X101
XMOS, Takt, QSPI-Flash
USB-Audio-Buchse, Versorgung XMOS
Nachbau der Forge-DSP-USB-Audio-Platine V4.0i (Original: Mark Duprau, pcbs/usb/com_audio/V40i, CC BY-NC-SA 4.0). Verbindungen über Netzlabels. Abweichungen vom Original sind in tools/parts.py mit PORT markiert (hardware#3).
